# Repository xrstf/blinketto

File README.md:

# Blinketto - Controlling my PixelPals remotely

This repository contains the source code, schematics and everything else for my
LED controller.

---

Blinketto was named after the Plinketto device in one of my favorite web series,
["Best of the Worst"](https://www.youtube.com/user/RedLetterMedia).

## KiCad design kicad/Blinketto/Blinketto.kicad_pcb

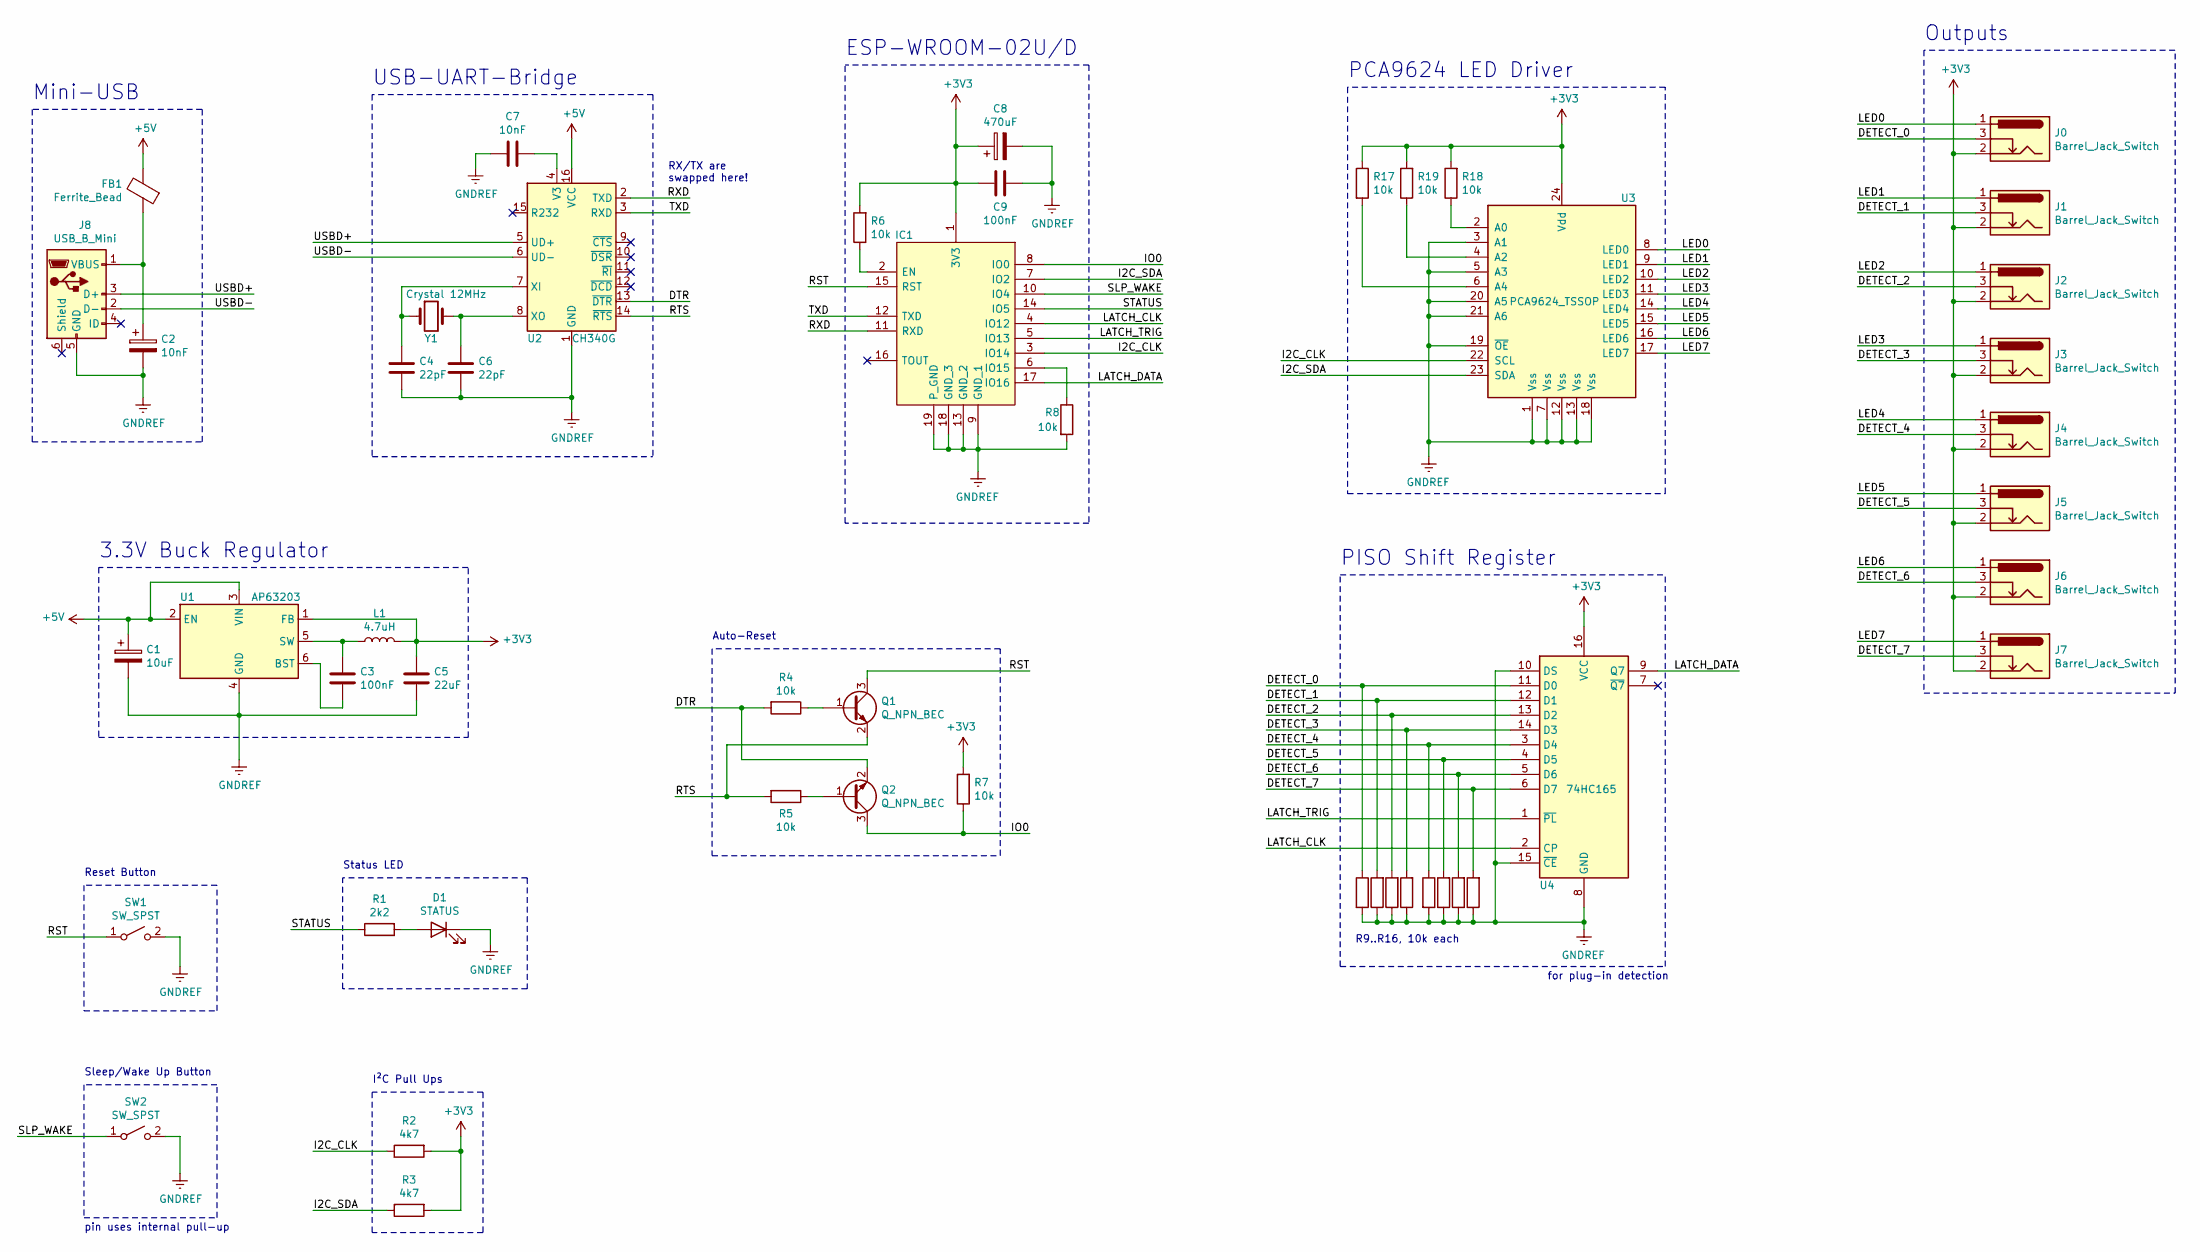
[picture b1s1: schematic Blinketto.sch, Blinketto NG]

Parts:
C1: 10uF; C_Elec_6.3x5.8
C2, C7: 10nF; C_0805_2012Metric
C3, C9: 100nF; C_0805_2012Metric
C4, C6: 22pF; C_0805_2012Metric
C5: 22uF; C_0805_2012Metric
C8: 470uF; CP_Elec_10x12.5
D1: STATUS; LED_1206_3216Metric_Pad1.42x1.75mm_HandSolder
FB1: Ferrite_Bead; L_1206_3216Metric_Pad1.42x1.75mm_HandSolder
IC1: ESP-WROOM-02U__4MB_; ESP-WROOM-02U
J0, J1, J2, J3, J4, J5, J6, J7: Barrel_Jack_Switch; Lumberg_1613-26_BarrelJack
J8: USB_B_Mini; USB_BWM_MIniUSB_THT_reichelt
L1: 4.7uH; Bourns_SRR0604_7.3x6.6mm
Q1, Q2: Q_NPN_BEC; SOT-23
R1: 2k2; R_0805_2012Metric
R2, R3: 4k7; R_0805_2012Metric
R4, R5, R6, R7, R8, R9, R10, R11, R12, R13, R14, R15, R16, R17, R18, R19: 10k; R_0805_2012Metric
SW1, SW2: SW_SPST; SW_Tactile_SPST_Angled_PTS645Vx83-2LFS
U1: AP63203; TSOT-23-6
U2: CH340G; SOIC-16_3.9x9.9mm_P1.27mm
U3: PCA9624_TSSOP; TSSOP-24_4.4x7.8mm_P0.65mm
U4: 74HC165; SO-16_3.9x9.9mm_P1.27mm
Y1: Crystal 12MHz; Crystal_SMD_HC49-SD

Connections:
+3V3: C5.2, C8.1, C9.1, IC1.1 (3V3), J0.2, J1.2, J2.2, J3.2, J4.2, J5.2, J6.2, J7.2, L1.2, R2.2, R3.2, R6.2, R7.2, R17.1, R18.2, R19.2, U1.1 (FB), U3.24 (Vdd), U4.16 (VCC)
+5V: C1.1, FB1.2, U1.2 (EN), U1.3 (VIN), U2.16 (VCC)
/DETECT_0: J0.3, R9.1, U4.11 (D0)
/DETECT_1: J1.3, R10.2, U4.12 (D1)
/DETECT_2: J2.3, R11.2, U4.13 (D2)
/DETECT_3: J3.3, R12.2, U4.14 (D3)
/DETECT_4: J4.3, R13.1, U4.3 (D4)
/DETECT_5: J5.3, R14.2, U4.4 (D5)
/DETECT_6: J6.3, R15.2, U4.5 (D6)
/DETECT_7: J7.3, R16.2, U4.6 (D7)
/DTR: Q2.2 (E), R4.2, U2.13 (~DTR)
/I2C_CLK: IC1.3 (IO14), R2.1, U3.22 (SCL)
/I2C_SDA: IC1.7 (IO2), R3.1, U3.23 (SDA)
/IO0: IC1.8 (IO0), Q2.3 (C), R7.1
/LATCH_CLK: IC1.4 (IO12), U4.2 (CP)
/LATCH_DATA: IC1.17 (IO16), U4.9 (Q7)
/LATCH_TRIG: IC1.5 (IO13), U4.1 (~PL)
/LED0: J0.1, U3.8 (LED0)
/LED1: J1.1, U3.9 (LED1)
/LED2: J2.1, U3.10 (LED2)
/LED3: J3.1, U3.11 (LED3)
/LED4: J4.1, U3.14 (LED4)
/LED5: J5.1, U3.15 (LED5)
/LED6: J6.1, U3.16 (LED6)
/LED7: J7.1, U3.17 (LED7)
/RST: IC1.15 (RST), Q1.3 (C), SW1.1 (A)
/RTS: Q1.2 (E), R5.2, U2.14 (~RTS)
/RXD: IC1.11 (RXD), U2.2 (TXD)
/SLP_WAKE: IC1.10 (IO4), SW2.1 (A)
/STATUS: IC1.14 (IO5), R1.1
/TXD: IC1.12 (TXD), U2.3 (RXD)
/USBD+: J8.3 (D+), U2.5 (UD+)
/USBD-: J8.2 (D-), U2.6 (UD-)
GNDREF: C1.2, C2.2, C4.1, C5.1, C6.1, C7.1, C8.2, C9.2, D1.1 (K), IC1.9 (GND_1), IC1.13 (GND_2), IC1.18 (GND_3), IC1.19 (P_GND), J8.5 (GND), R8.2, R9.2, R10.1, R11.1, R12.1, R13.2, R14.1, R15.1, R16.1, SW1.2 (B), SW2.2 (B), U1.4 (GND), U2.1 (GND), U3.1 (Vss), U3.3 (A1), U3.5 (A3), U3.7 (Vss), U3.12 (Vss), U3.13 (Vss), U3.18 (Vss), U3.19 (~OE), U3.20 (A5), U3.21 (A6), U4.8 (GND), U4.10 (DS), U4.15 (~CE)
unnamed: C2.1, FB1.1, J8.1 (VBUS)
unnamed: C3.1, U1.6 (BST)
unnamed: C3.2, L1.1, U1.5 (SW)
unnamed: C4.2, U2.7 (XI), Y1.1
unnamed: C6.2, U2.8 (XO), Y1.2
unnamed: C7.2, U2.4 (V3)
unnamed: D1.2 (A), R1.2
unnamed: IC1.2 (EN), R6.1
unnamed: IC1.6 (IO15), R8.1
unnamed: Q1.1 (B), R4.1
unnamed: Q2.1 (B), R5.1
unnamed: R17.2, U3.6 (A4)
unnamed: R18.1, U3.2 (A0)
unnamed: R19.1, U3.4 (A2)

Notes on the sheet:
Mini-USB
Status LED
Auto-Reset
ESP-WROOM-02U/D
Reset Button
3.3V Buck Regulator
PCA9624 LED Driver
PISO Shift Register
for plug-in detection
Outputs
Sleep/Wake Up Button
I²C Pull Ups
RX/TX are swapped here!
USB-UART-Bridge
pin uses internal pull-up
R9..R16, 10k each

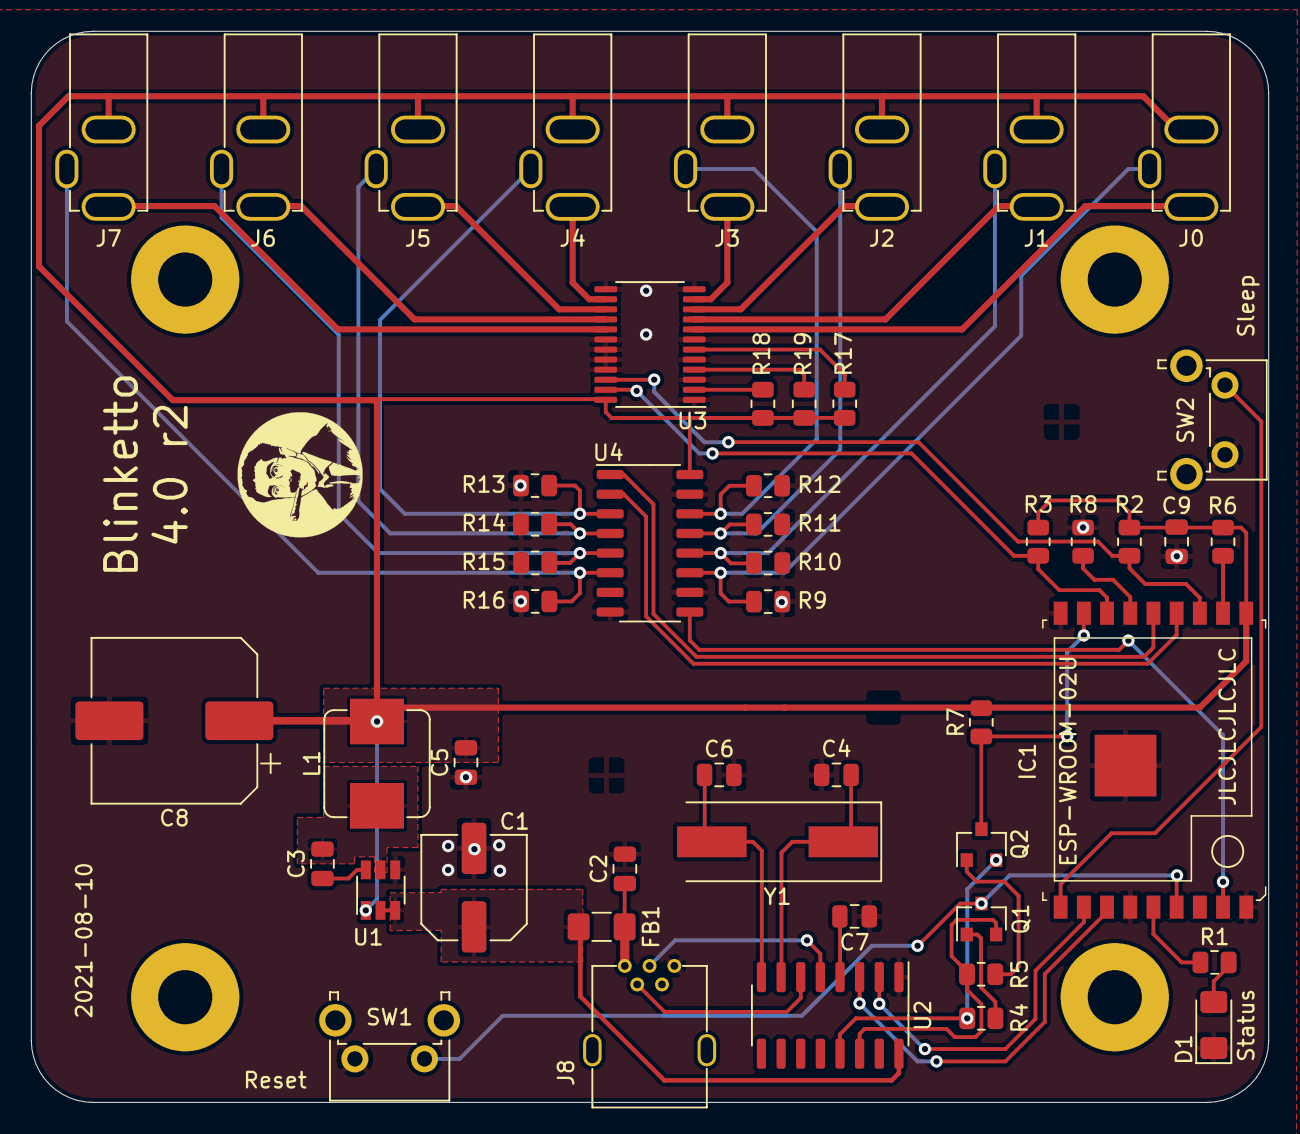
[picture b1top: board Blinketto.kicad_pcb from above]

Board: 2 copper layers, 80.0 x 69.2 mm, 50 parts (0 on the bottom side), 48 nets.

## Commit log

2021-08-21 initial commit of Blinketto 4 rev2
2021-08-21 add docs
2021-08-21 add readme
2021-08-21 add source code
2021-08-21 add history
2021-08-21 fix typo
2021-08-29 add webapp, better sleep mode, minimize JSON size to prevent OOM errors
